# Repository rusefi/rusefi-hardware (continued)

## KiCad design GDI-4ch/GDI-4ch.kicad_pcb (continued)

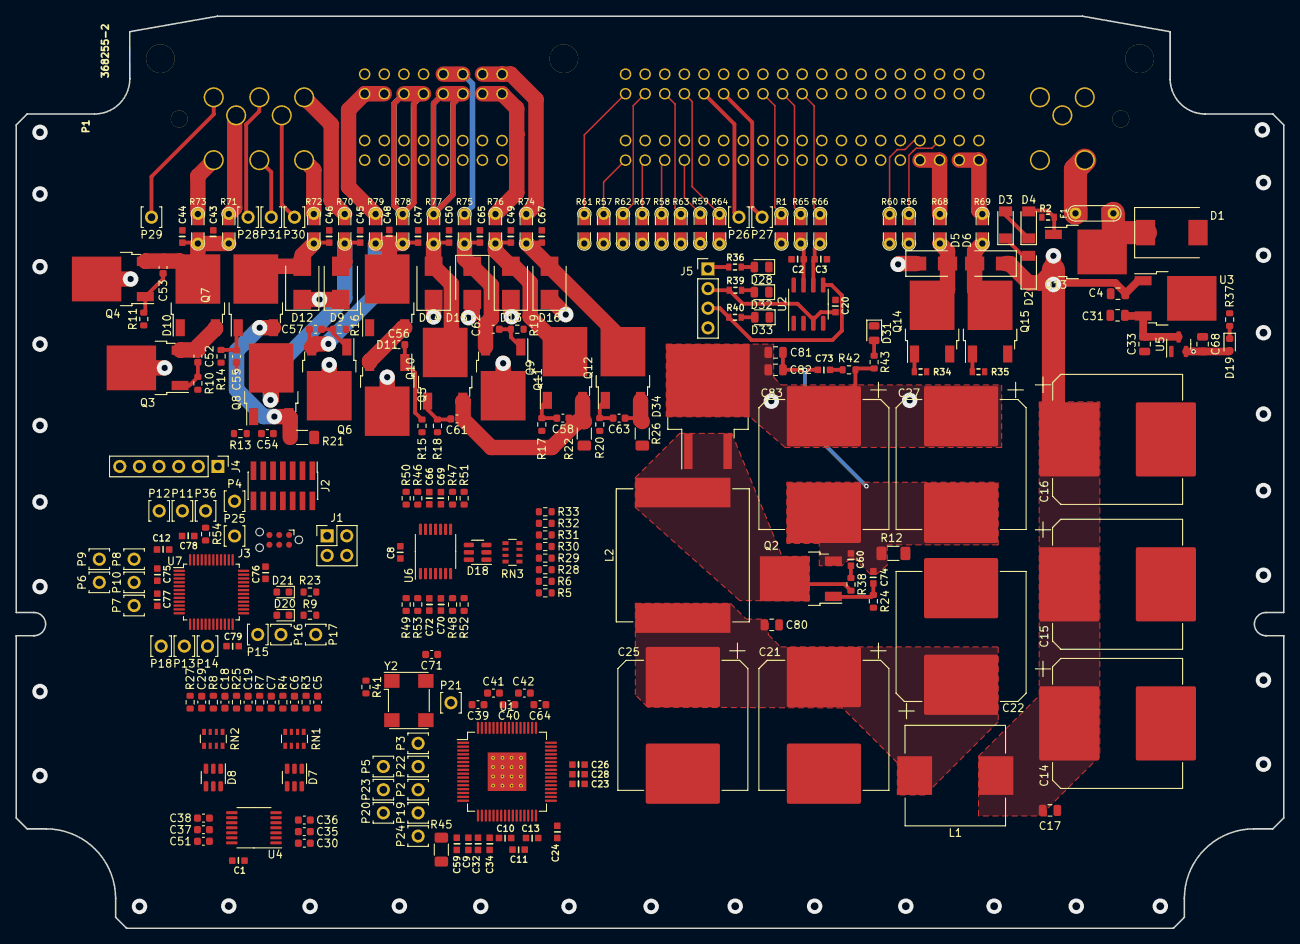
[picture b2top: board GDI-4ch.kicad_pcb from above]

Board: 4 copper layers, 164.0 x 118.0 mm, 250 parts (0 on the bottom side), 176 nets.

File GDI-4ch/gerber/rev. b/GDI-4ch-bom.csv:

Comment,Designator,Footprint,LCSC
"100n","C1,C8,C20,C23,C28,C32,C34,C59,C66,C69,C70,C72,C75,C76,C77,C78,C79","hellen-one-common:C0603","C14663"
"330p","C10,C11,C13,C24,C60,C73","hellen-one-common:C0603","C576850"
"4.7u","C12,C26","hellen-one-common:C0603","C19666"
"390uF","C14,C15,C16,C21,C22,C25,C27,C83","Capacitor_SMD:CP_Elec_16x17.5","C487421"
"0.22uF","C17,C80,C81,C82","Capacitor_SMD:C_0805_2012Metric","C342873"
"47p","C2,C3","hellen-one-common:C0603","C1671"
"0.33uF","C39,C40,C41,C42,C64","Capacitor_SMD:C_0603_1608Metric","C1615"
"10u","C4,C31,C33,C68","Capacitor_SMD:C_0805_2012Metric","C15850"
"4700p","C43,C44,C45,C46,C47,C48,C49,C50,C65,C67","hellen-one-common:C0603","C342899"
"1000pF","C5,C6,C7,C18,C19,C29,C30,C35,C36,C37,C38,C51,C52,C53,C54,C55,C56,C57,C58,C61,C62,C63,C71","Capacitor_SMD:C_0603_1608Metric","C106247"
"470p","C74","hellen-one-common:C0603","C326973"
"1u","C9","hellen-one-common:C0603","C15849"
"SMCJ22CA","D1","Diode_SMD:D_SMC","C310038"
"SBR10200CTL","D10,D11","Package_TO_SOT_SMD:TO-252-2","C135494"
"WHITE","D19","LED_SMD:LED_0603_1608Metric","C2290"
"ZMM5V6","D2,D3,D4","Diode_SMD:D_MiniMELF","C8062"
"BLUE","D20","LED_SMD:LED_0603_1608Metric","C72041"
"GREEN","D21","LED_SMD:LED_0603_1608Metric","C72043"
"LED_Small","D28,D31,D32,D33","LED_SMD:LED_0805_2012Metric","C2296"
"SDURB1020CT","D34","Package_TO_SOT_SMD:TO-263-2","C260365"
"D_Schottky","D5,D6","Diode_SMD:D_SMA","C8678"
"SRV05-4","D7,D8,D18","Package_TO_SOT_SMD:SOT-23-6","C85364"
"STPS2H100UY","D9,D12,D13,D14,D15,D16","Diode_SMD:D_SMB","C163541"
"Fuse-Pad-Pad","F1","hellen-one-common:PAD-1206-PAD","C310989"
"RUSEFI_LOGO","G1","kicad6-libraries:rusefi_logo",""
"Conn_02x02_Odd_Even","J1","Connector_PinHeader_2.54mm:PinHeader_2x02_P2.54mm_Vertical",""
"FTSH-107-01-F-DV-K","J2","Connector_PinHeader_1.27mm:PinHeader_2x07_P1.27mm_Vertical_SMD",""
"Conn_01x06","J4","Connector_PinHeader_2.54mm:PinHeader_1x06_P2.54mm_Vertical",""
"Conn_01x04","J5","Connector_PinHeader_2.54mm:PinHeader_1x04_P2.54mm_Vertical",""
"6.8uH","L1","Inductor_SMD:L_Wuerth_HCI-1350","C380073"
"10uH","L2","Inductor_SMD:L_Vishay_IHLP-6767","C237980"
"368255-2","P1","kicad6-libraries:TE_368255-2",""
"Pad","P2,P3,P4,P5,P6,P7,P8,P9,P10,P11,P18,P19,P20,P25,P26,P27,P28,P29,P30,P31,P32,P36","hellen-one-common:PAD-TH",""
"AOD4185","Q13","Package_TO_SOT_SMD:TO-252-2","C400894"
"VND14NV04TR-E","Q14,Q15","Package_TO_SOT_SMD:TO-252-2","C2649436"
"BUK9230-100B","Q2,Q3,Q4,Q5,Q6,Q7,Q8,Q9,Q10,Q11,Q12","Package_TO_SOT_SMD:TO-252-2","C89735"
"DNP","R1,R44,R55,R60,R80,R81,R82,R83","hellen-one-common:PAD-0805-PAD",""
"10","R10,R11,R13,R14,R15,R16,R17,R18,R19,R20,R24","Resistor_SMD:R_0603_1608Metric","C22859"
"0.01","R12,R21,R22,R26,R45","kicad6-libraries:Shunt_1206","C309628"
"10k","R2,R34,R35","hellen-one-common:R0603","C25804"
"1K","R3,R4,R7,R8,R9,R23,R25,R27,R37","Resistor_SMD:R_0603_1608Metric","C21190"
"5.1k","R36","hellen-one-common:R0603","C23186"
"5.1","R38,R42","Resistor_SMD:R_0603_1608Metric","C25197"
"1.6k","R39","hellen-one-common:R0603","C22847"
"750","R40","hellen-one-common:R0603","C23241"
"75K","R43","Resistor_SMD:R_0603_1608Metric","C23242"
"6.8K","R46,R47,R48,R49","Resistor_SMD:R_0603_1608Metric","C23212"
"DNP","R5,R28,R30,R32","Resistor_SMD:R_0603_1608Metric",""
"10K","R50,R51,R52,R53,R54","Resistor_SMD:R_0603_1608Metric","C25804"
"Jumper-Pad-Pad","R56,R57,R58,R59,R61,R62,R63,R64,R65,R66,R67,R68,R69,R70,R71,R72,R73,R74,R75,R76,R77,R78,R79","hellen-one-common:PAD-0805-PAD","C17477"
"470K","R6,R29,R31,R33","Resistor_SMD:R_0603_1608Metric","C23178"
"10k","RN1,RN2,RN3","Resistor_SMD:R_Array_Convex_4x0603","C29718"
"MC33816","U1","Package_QFP:LQFP-64-1EP_10x10mm_P0.5mm_EP5x5mm_ThermalVias",""
"TJA1051T-3","U2","Package_SO:SOIC-8_3.9x4.9mm_P1.27mm","C38695"
"LM78M05_TO252","U3","Package_TO_SOT_SMD:TO-252-2","C58069"
"74HC14","U4","Package_SO:TSSOP-14_4.4x5mm_P0.65mm","C5606"
"XC6206P332MR","U5","Package_TO_SOT_SMD:SOT-23","C5446"
"MCP6004","U6","Package_SO:TSSOP-14_4.4x5mm_P0.65mm","C248577"
"STM32F103C8Tx","U7","Package_QFP:LQFP-48_7x7mm_P0.5mm","C8734"
"1MHz","Y2","Oscillator:Oscillator_SMD_Diodes_FN-4Pin_7.0x5.0mm","C70608"

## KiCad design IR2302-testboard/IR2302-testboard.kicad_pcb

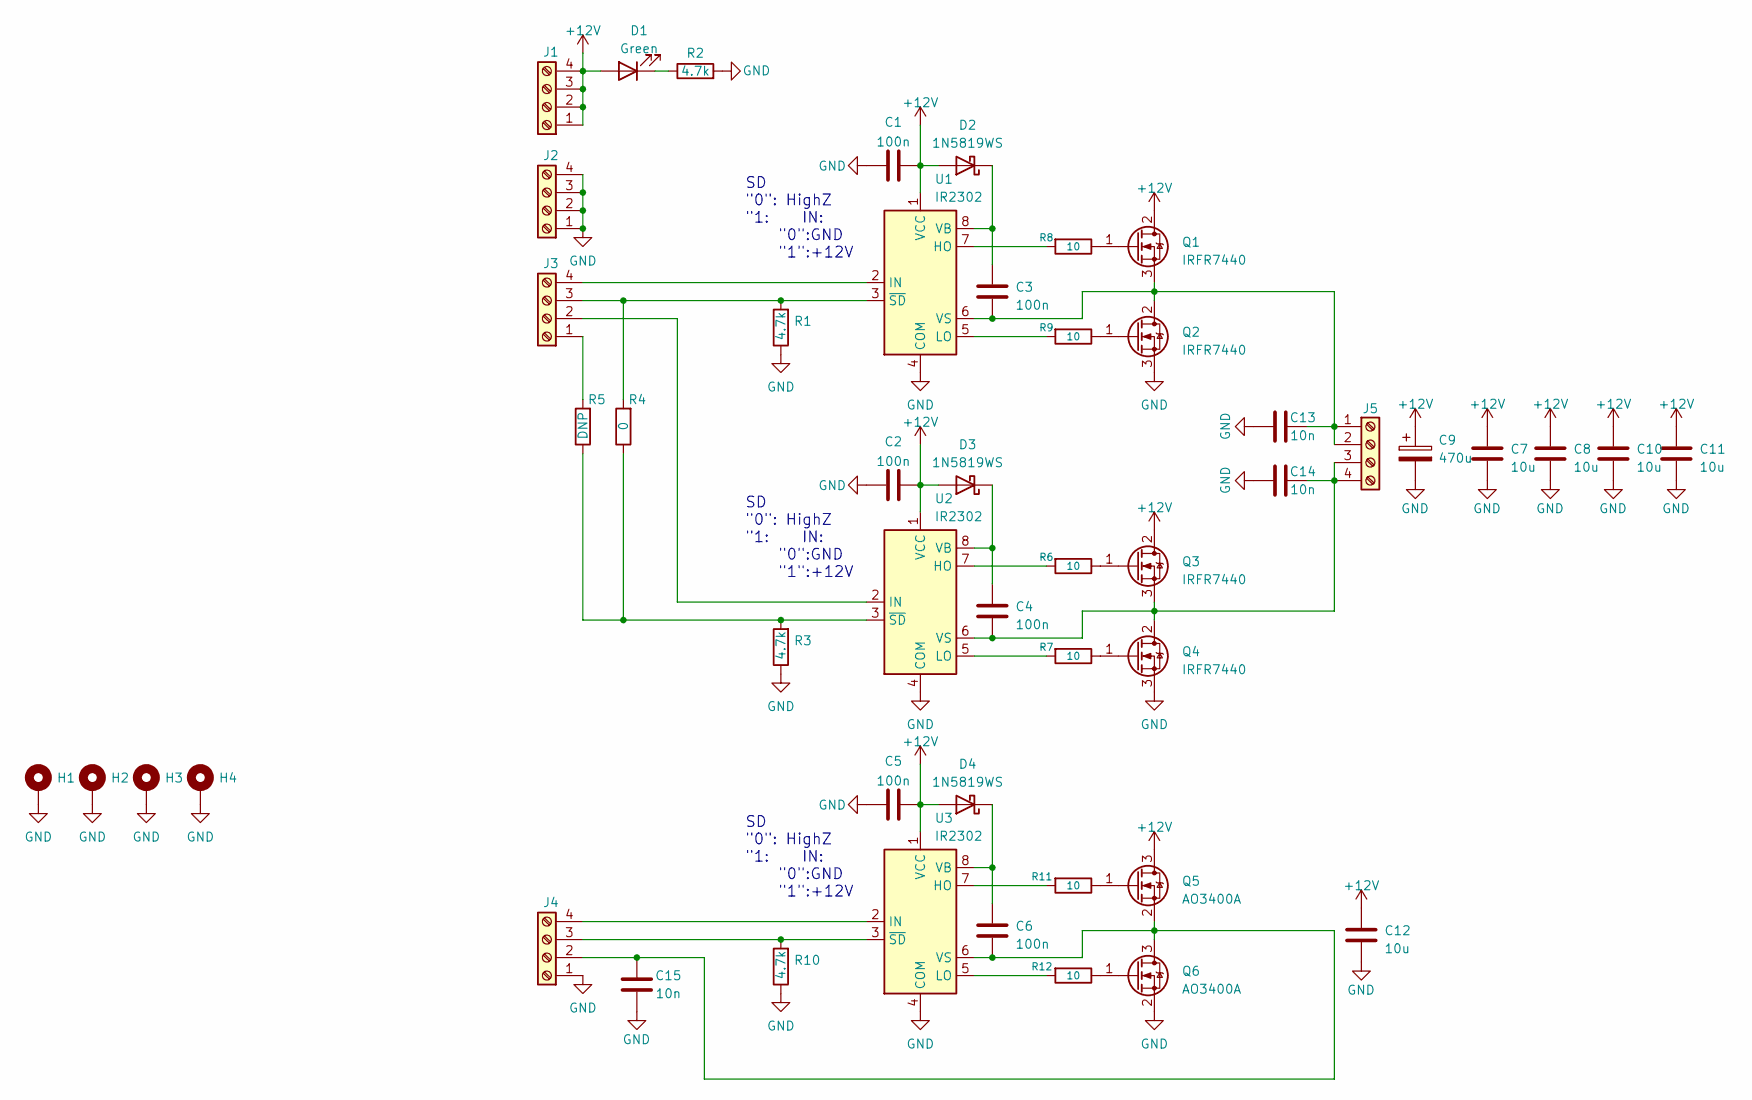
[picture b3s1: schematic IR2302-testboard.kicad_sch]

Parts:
C1, C2, C3, C4, C5, C6: 100n; C_0603_1608Metric_Pad1.08x0.95mm_HandSolder; LCSC C14663
C7, C8, C10, C11, C12: 10u; C_0805_2012Metric_Pad1.18x1.45mm_HandSolder; LCSC C15850
C9: 470u; CP_Elec_10x10.5; LCSC C72518
C13, C14, C15: 10n; C_0603_1608Metric_Pad1.08x0.95mm_HandSolder; LCSC C57112
D1: Green; LED_0805_2012Metric_Pad1.15x1.40mm_HandSolder; LCSC C2297
D2, D3, D4: 1N5819WS; D_SOD-323; LCSC C191023
H1, H2, H3, H4: MountingHole_Pad; MountingHole_3.2mm_M3_Pad_Via
J1, J2, J3, J4, J5: Screw_Terminal_01x04; TerminalBlock_MetzConnect_Type055_RT01504HDWU_1x04_P5.00mm_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; LCSC C173286
Q1, Q2, Q3, Q4: IRFR7440; TO-252-2; LCSC C97244
Q5, Q6: AO3400A; SOT-23; LCSC C20917
R1, R2, R3, R10: 4.7k; R_0603_1608Metric_Pad0.98x0.95mm_HandSolder; LCSC C23162
R4: 0; R_0603_1608Metric_Pad0.98x0.95mm_HandSolder; LCSC C21189
R5: DNP; R_0603_1608Metric_Pad0.98x0.95mm_HandSolder
R6, R7, R8, R9, R11, R12: 10; R_0603_1608Metric; LCSC C22859
U1, U2, U3: IR2302; SO-8_3.9x4.9mm_P1.27mm; LCSC C148147

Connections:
+12V: C1.2, C2.2, C5.2, C7.2, C8.2, C9.1, C10.2, C11.2, C12.2, D1.2 (A), D2.2 (A), D3.2 (A), D4.2 (A), J1.1, J1.2, J1.3, J1.4, Q1.2 (D), Q3.2 (D), Q5.3 (D), U1.1 (VCC), U2.1 (VCC), U3.1 (VCC)
GND: C1.1, C2.1, C5.1, C7.1, C8.1, C9.2, C10.1, C11.1, C12.1, C13.1, C14.1, C15.1, H1.1, H2.1, H3.1, H4.1, J2.1, J2.2, J2.3, J2.4, J4.1, Q2.3 (S), Q4.3 (S), Q6.2 (S), R1.1, R2.2, R3.1, R10.1, U1.4 (COM), U2.4 (COM), U3.4 (COM)
unnamed: D1.1 (K), R2.1
unnamed: C3.1, D2.1 (K), U1.8 (VB)
unnamed: C4.1, D3.1 (K), U2.8 (VB)
unnamed: C6.1, D4.1 (K), U3.8 (VB)
unnamed: J3.1, R5.2
unnamed: J3.2, U2.2 (IN)
unnamed: J3.3, R1.2, R4.2, U1.3 (~SD)
unnamed: J3.4, U1.2 (IN)
unnamed: C6.2, C15.2, J4.2, Q5.2 (S), Q6.3 (D), U3.6 (VS)
unnamed: J4.3, R10.2, U3.3 (~SD)
unnamed: J4.4, U3.2 (IN)
unnamed: C3.2, C13.2, J5.1, J5.2, Q1.3 (S), Q2.2 (D), U1.6 (VS)
unnamed: C4.2, C14.2, J5.3, J5.4, Q3.3 (S), Q4.2 (D), U2.6 (VS)
unnamed: Q1.1 (G), R8.1
unnamed: Q2.1 (G), R9.1
unnamed: Q3.1 (G), R6.1
unnamed: Q4.1 (G), R7.1
unnamed: Q5.1 (G), R11.1
unnamed: Q6.1 (G), R12.1
unnamed: R8.2, U1.7 (HO)
unnamed: R9.2, U1.5 (LO)
unnamed: R6.2, U2.7 (HO)
unnamed: R7.2, U2.5 (LO)
unnamed: R3.2, R4.1, R5.1, U2.3 (~SD)
unnamed: R11.2, U3.7 (HO)
unnamed: R12.2, U3.5 (LO)

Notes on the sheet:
SD "0": HighZ "1: IN: "0":GND "1":+12V

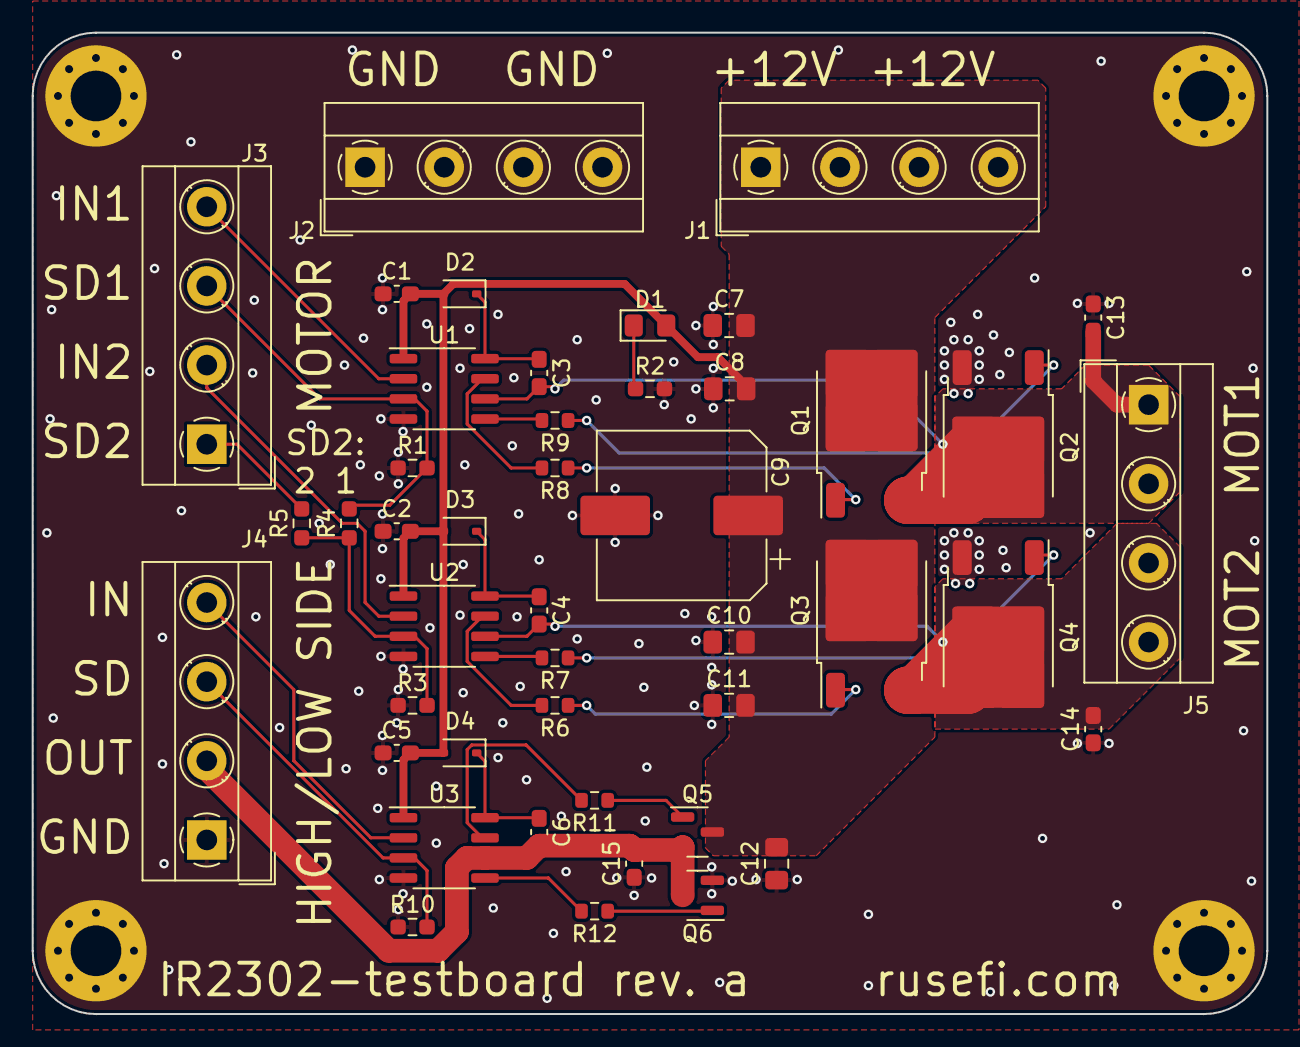
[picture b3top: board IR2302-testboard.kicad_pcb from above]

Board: 2 copper layers, 78.0 x 62.0 mm, 49 parts (0 on the bottom side), 28 nets.

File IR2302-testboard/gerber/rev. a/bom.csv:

Designator,Footprint,Quantity,Value,LCSC Part #
"C1, C2, C3, C4, C5, C6",0603,6,100n,C14663
"C10, C11, C12, C7, C8",0805,5,10u,C15850
"C13, C14, C15",0603,3,10n,C57112
C9,CP_Elec_10x10.5,1,470u,C72518
D1,0805,1,Green,C2297
"D2, D3, D4",D_SOD-323,3,1N5819WS,C191023
"H1, H2, H3, H4",MountingHole_3.2mm_M3_Pad_Via,4,MountingHole_Pad,
"J1, J2, J3, J4, J5",TerminalBlock_MetzConnect_Type055_RT01504HDWU_1x04_P5.00mm_Horizontal,5,Screw_Terminal_01x04,C173286
"Q1, Q2, Q3, Q4",TO-252-2,4,IRFR7440,C97244
"Q5, Q6",SOT-23,2,AO3400A,C20917
"R1, R10, R2, R3",0603,4,4.7k,C23162
"R11, R12, R6, R7, R8, R9",0603,6,10,C22859
R4,0603,1,0,C21189
R5,0603,1,DNP,
"U1, U2, U3",SO-8_3.9x4.9mm_P1.27mm,3,IR2302,C148147

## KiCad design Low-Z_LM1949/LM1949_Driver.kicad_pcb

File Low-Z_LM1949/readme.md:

https://www.ti.com/product/LM1949

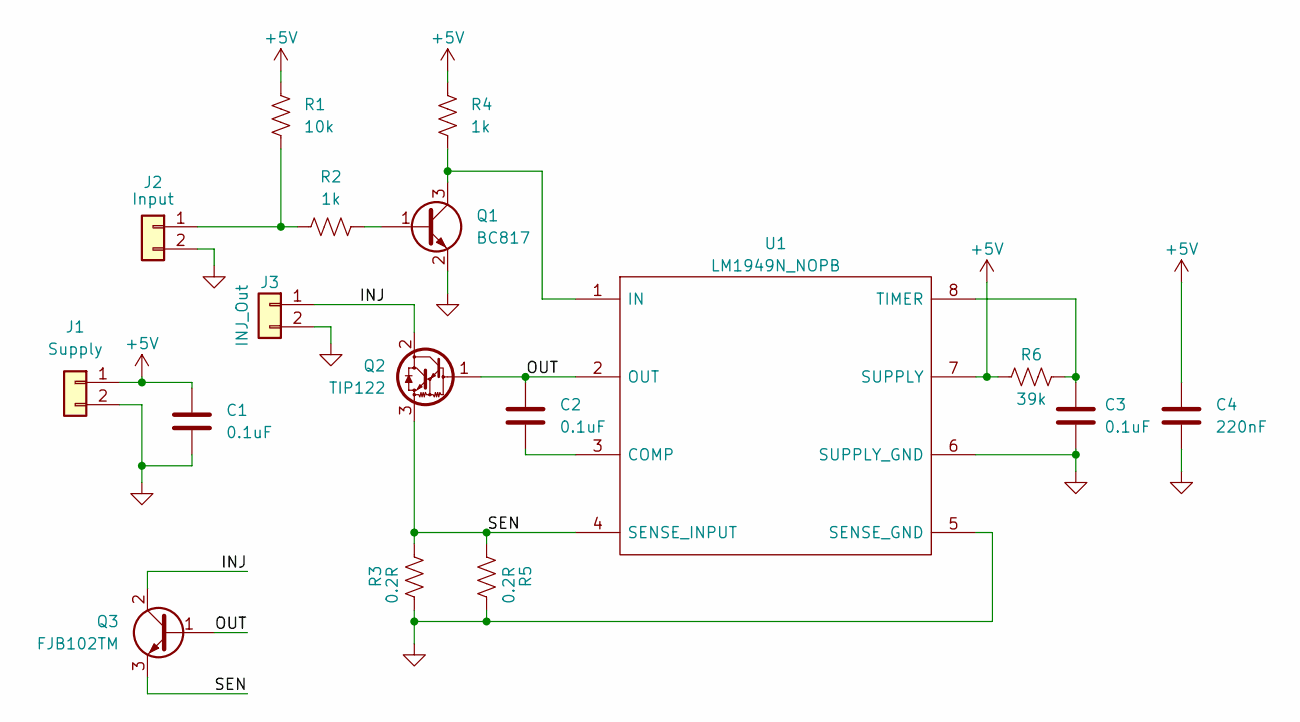
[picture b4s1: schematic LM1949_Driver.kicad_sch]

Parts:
C1, C2, C3: 0.1uF; C_0805_2012Metric_Pad1.18x1.45mm_HandSolder; JLC Pt. Num C126469
C4: 220nF; CP_EIA-3216-18_Kemet-A_Pad1.58x1.35mm_HandSolder; JLC Pt. Num C11364
J1: Supply; TerminalBlock_Phoenix_PT-1,5-2-5.0-H_1x02_P5.00mm_Horizontal; JLC Pt. Num NC
J2: Input; TerminalBlock_Phoenix_PT-1,5-2-5.0-H_1x02_P5.00mm_Horizontal; JLC Pt. Num NC
J3: INJ_Out; TerminalBlock_Phoenix_PT-1,5-2-5.0-H_1x02_P5.00mm_Horizontal; JLC Pt. Num NC
Q1: BC817; SOT-23; JLC Pt. Num C475629
Q2: TIP122; TO-220-3_Vertical; JLC Pt. Num C16283
Q3: FJB102TM; TO-263-2; JLC Pt. Num NC
R1: 10k; R_0805_2012Metric_Pad1.20x1.40mm_HandSolder; JLC Pt. Num C416062
R2, R4: 1k; R_0805_2012Metric_Pad1.20x1.40mm_HandSolder; JLC Pt. Num C100046
R3, R5: 0.2R; R_2512_6332Metric_Pad1.40x3.35mm_HandSolder; JLC Pt. Num C176047
R6: 39k; R_0805_2012Metric_Pad1.20x1.40mm_HandSolder; JLC Pt. Num C416101
U1: LM1949N_NOPB; DIP-8_W7.62mm_LongPads; JLC Pt. Num NC

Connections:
+5V: C1.1, C4.1, J1.1, R1.1, R4.1, R6.1, U1.7 (SUPPLY)
/INJ: J3.1, Q2.2 (C), Q3.2 (C)
/OUT: C2.1, Q2.1 (B), Q3.1 (B), U1.2 (OUT)
/SEN: Q2.3 (E), Q3.3 (E), R3.1, R5.1, U1.4 (SENSE_INPUT)
GND: C1.2, C3.2, C4.2, J1.2, J2.2, J3.2, Q1.2 (E), R3.2, R5.2, U1.5 (SENSE_GND), U1.6 (SUPPLY_GND)
unnamed: C2.2, U1.3 (COMP)
unnamed: C3.1, R6.2, U1.8 (TIMER)
unnamed: J2.1, R1.2, R2.1
unnamed: Q1.1 (B), R2.2
unnamed: Q1.3 (C), R4.2, U1.1 (IN)

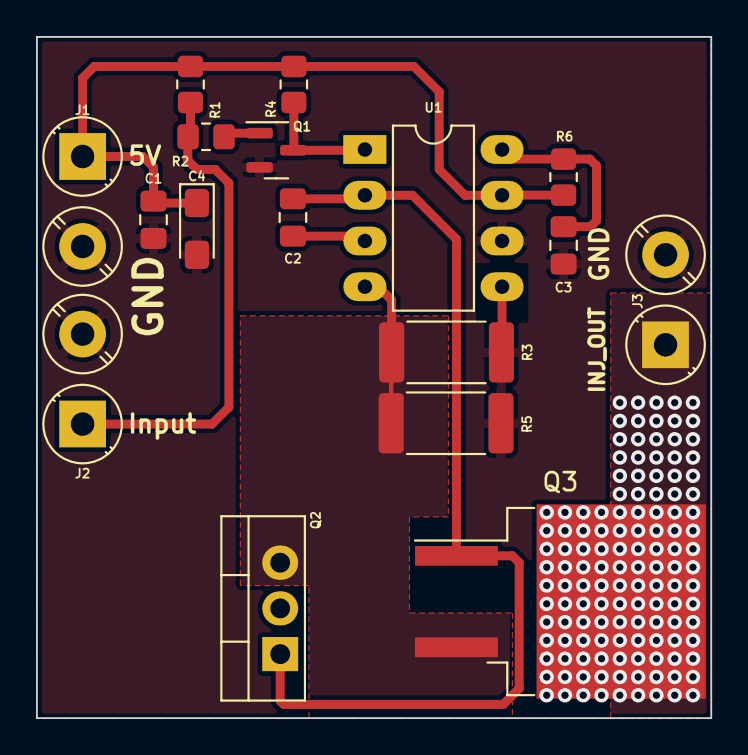
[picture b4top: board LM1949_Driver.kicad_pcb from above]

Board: 2 copper layers, 37.5 x 37.8 mm, 17 parts (0 on the bottom side), 10 nets.

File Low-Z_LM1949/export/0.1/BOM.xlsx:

Comment | Designator | Footprint | LCSC Part Number
0.1uF | C1,C2,C3 | Capacitor_SMD:C_0805_2012Metric_Pad1.18x1.45mm_HandSolder | C126469
220nF | C4 | Capacitor_Tantalum_SMD:CP_EIA-3216-18_Kemet-A_Pad1.58x1.35mm_HandSolder | C11364
BC817 | Q1 | Package_TO_SOT_SMD:SOT-23 | C475629
TIP122 | Q2 | Package_TO_SOT_THT:TO-220-3_Vertical | C16283
10k | R1 | Resistor_SMD:R_0805_2012Metric_Pad1.20x1.40mm_HandSolder | C416062
1k | R2,R4 | Resistor_SMD:R_0805_2012Metric_Pad1.20x1.40mm_HandSolder | C100046
0.2R | R3,R5 | Resistor_SMD:R_0805_2012Metric_Pad1.20x1.40mm_HandSolder | C176047
39k | R6 | Resistor_SMD:R_0805_2012Metric_Pad1.20x1.40mm_HandSolder | C416101

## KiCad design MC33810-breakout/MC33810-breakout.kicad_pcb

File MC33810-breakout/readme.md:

https://www.nxp.com/products/power-management/smart-switches-and-drivers/low-side-switches/automotive-engine-control-ic:MC33810

https://github.com/andreika-git/hellen-one/issues/173

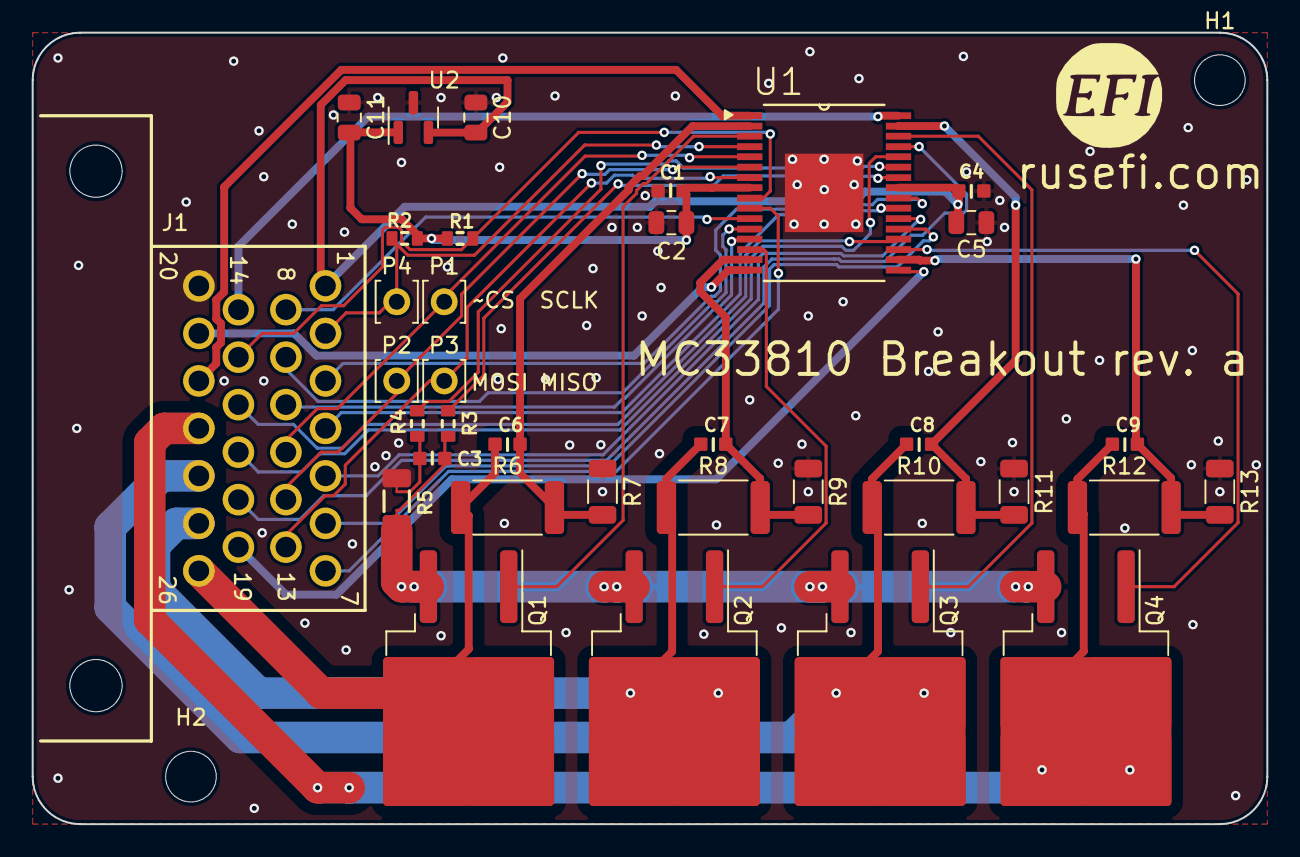
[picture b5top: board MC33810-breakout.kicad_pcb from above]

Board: 2 copper layers, 78.0 x 50.0 mm, 38 parts (0 on the bottom side), 40 nets.

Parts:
C1, C4, C6, C7, C8, C9: 100n; C0603
C2, C5, C10, C11: 10u; C_0805_2012Metric
C3: 100p; C0603
G1: RUSEFI_LOGO; rusefi_logo
H1, H2: M3; MountingHole_3.2mm_M3_ISO14580
J1: 6473423-1
P1, P2, P3, P4: Pad; PAD-TH
Q1, Q2, Q3, Q4: ISL9V3040S3S; TO-263-2
R1, R2: 10k; R0603
R3, R4: 100; R0603
R5: 0.02; Shunt_1206
R6, R8, R10, R12: 36k; R_2512_6332Metric
R7, R9, R11, R13: 4.02k; R_1206_3216Metric
U1: MCZ33810EK; Mcz33810
U2: XC6202P332MR-G; SOT-23

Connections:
+3.3V: C1.1, C2.2, C11.2, R1.2, R2.2, U1.8 (VDD), U2.1 (VO)
+BATT: C4.1, C5.2, C10.2, J1.1 (1B), U1.25 (VPWR), U2.2 (VI)
/IGN1: J1.3 (3B), U1.24 (GIN0)
/IGN2: J1.4 (4B), U1.23 (GIN1)
/IGN3: J1.5 (5B), U1.22 (GIN2)
/IGN4: J1.6 (6B), U1.21 (GIN3)
/INJ1: J1.7 (7B), U1.10 (DIN0)
/INJ2: J1.8 (8B), U1.11 (DIN1)
/INJ3: J1.9 (9B), U1.12 (DIN2)
/INJ4: J1.10 (10B), U1.13 (DIN3)
/MAXI: J1.18 (18B), U1.29 (MAXI)
/MISO: J1.13 (13B), P3.1, U1.7 (SO)
/MOSI: J1.12 (12B), P2.1, U1.6 (SI)
/NOMI: J1.17 (17B), U1.28 (NOMI)
/OUT_IGN1: C6.1, J1.26 (26B), Q1.2 (C), R6.1
/OUT_IGN2: C7.1, J1.25 (25B), Q2.2 (C), R8.1
/OUT_IGN3: C8.1, J1.24 (24B), Q3.2 (C), R10.1
/OUT_IGN4: C9.1, J1.23 (23B), Q4.2 (C), R12.1
/OUT_INJ1: J1.22 (22B), U1.1 (OUT0)
/OUT_INJ2: J1.21 (21B), U1.16 (OUT1)
/OUT_INJ3: J1.14 (14B), U1.32 (OUT2)
/OUT_INJ4: J1.19 (19B), U1.17 (OUT3)
/SCLK: J1.11 (11B), P1.1, U1.5 (SCLK)
/~CS: J1.2 (2B), P4.1, R2.1, U1.4 (~CS)
/~OUTEN: J1.15 (15B), R1.1, U1.9 (~OUTEN)
/~SPKDUR: J1.16 (16B), U1.20 (~SPKDUR)
GND: C1.2, C2.1, C4.2, C5.1, C10.1, C11.1, J1.20 (20B), R5.4, R7.2, R9.2, R11.2, R13.2, U1.33 (GND), U2.3 (GND)
unnamed: C3.1, R3.2, R5.2
unnamed: C3.2, R4.2, R5.3
unnamed: Q1.3 (E), Q2.3 (E), Q3.3 (E), Q4.3 (E), R5.1
unnamed: Q1.1 (G), U1.3 (GD0)
unnamed: Q2.1 (G), U1.14 (GD1)
unnamed: Q3.1 (G), U1.30 (GD2)
unnamed: Q4.1 (G), U1.19 (GD3)
unnamed: C6.2, R6.2, R7.1, U1.2 (FB0)
unnamed: C7.2, R8.2, R9.1, U1.15 (FB1)
unnamed: C8.2, R10.2, R11.1, U1.31 (FB2)
unnamed: C9.2, R12.2, R13.1, U1.18 (FB3)
unnamed: R4.1, U1.27 (RSN)
unnamed: R3.1, U1.26 (RSP)

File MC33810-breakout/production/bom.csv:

Designator,Footprint,Quantity,Value,LCSC Part #
"C1, C4, C6, C7, C8, C9",C0603,6,100n,C14663
"C10, C11, C2, C5",0805,4,10u,C15850
C3,C0603,1,100p,C14858
G1,rusefi_logo,1,RUSEFI_LOGO,
"H1, H2",MountingHole_3.2mm_M3_ISO14580,2,M3,
J1,6473423-1,1,6473423-1,
"P1, P2, P3, P4",PAD-TH,4,Pad,
"Q1, Q2, Q3, Q4",TO-263-2,4,ISL9V3040S3S,C898702
"R1, R2",R0603,2,10k,C25804
"R10, R12, R6, R8",2512,4,36k,C474088
"R11, R13, R7, R9",1206,4,4.02k,C274026
"R3, R4",R0603,2,100,C22775
R5,Shunt_1206,1,0.02,C728292
U1,Mcz33810,1,MCZ33810EK,C3192631
U2,SOT-23,1,XC6202P332MR-G,C47374

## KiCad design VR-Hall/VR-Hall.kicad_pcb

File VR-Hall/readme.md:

VR/Hall mixing test board

Problem statement: do do not have x8 or x10 position sensor inputs on stm32, in order to handle any combination of x5 hall and x3/x5 VRs we would need to mix each VR with Hall

We are looking to confirm that VR signal (in this case from MAX9924) could be mixed with Hall signal into same/shared digital signal

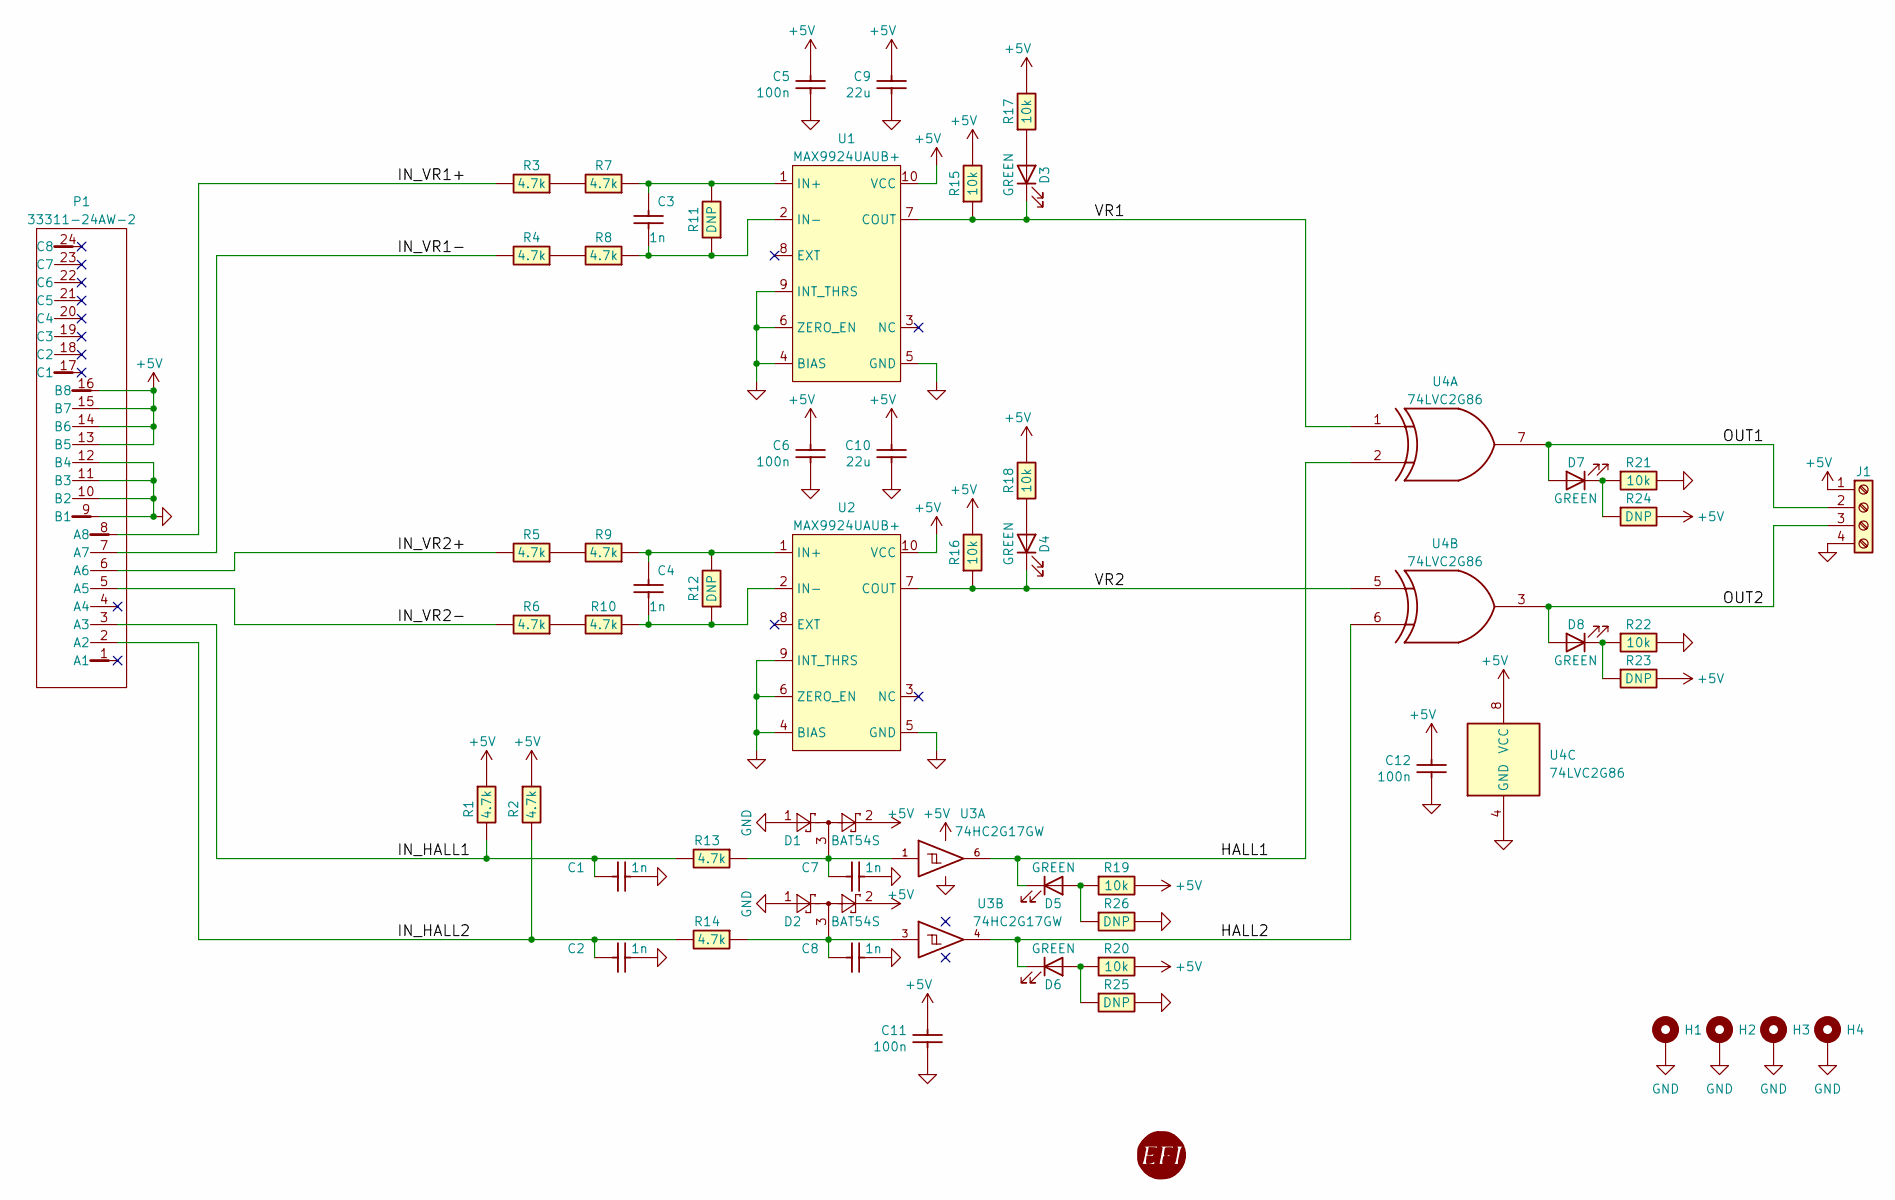
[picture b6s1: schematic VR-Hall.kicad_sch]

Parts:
C1, C2, C3, C4, C7, C8: 1n; C0603; LCSC C1588
C5, C6, C11, C12: 100n; C0603; LCSC C14663
C9, C10: 22u; C0603; LCSC C59461
D1, D2: BAT54S; SOT-23; LCSC C408389
D3, D4, D5, D6, D7, D8: GREEN; LED_0603_1608Metric; LCSC C72043
G1: RUSEFI_LOGO; rusefi_logo
H1, H2, H3, H4: MountingHole_Pad; MountingHole_3.2mm_M3_Pad_Via
J1: DNP; TerminalBlock_MetzConnect_Type055_RT01504HDWU_1x04_P5.00mm_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
P1: 33311-24AW-2
R1, R2, R13, R14: 4.7k; R0603; LCSC C23162
R3, R4, R5, R6, R7, R8, R9, R10: 4.7k; R1206; LCSC C17936
R11, R12, R23, R24, R25, R26: DNP; R0603
R15, R16, R17, R18, R19, R20, R21, R22: 10k; R0603; LCSC C25804
U1, U2: MAX9924UAUB+; MSOP-10_3x3mm_P0.5mm; LCSC C143633
U3: 74HC2G17GW; SOT-363; LCSC C94189
U4: 74LVC2G86; MSOP-8_3x3mm_P0.65mm; LCSC C130023

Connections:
+5V: C5.2, C6.2, C9.2, C10.2, C11.2, C12.2, D1.2, D2.2, J1.1, P1.13 (B5), P1.14 (B6), P1.15 (B7), P1.16 (B8), R1.1, R2.1, R15.2, R16.2, R17.2, R18.2, R19.2, R20.2, R23.2, R24.2, U1.10 (VCC), U2.10 (VCC), U3.5 (VCC), U4.8 (VCC)
/HALL1: D5.1 (K), U3.6, U4.2
/HALL2: D6.1 (K), U3.4, U4.6
/IN_HALL1: C1.1, P1.3 (A3), R1.2, R13.2
/IN_HALL2: C2.1, P1.2 (A2), R2.2, R14.2
/IN_VR1+: P1.8 (A8), R3.2
/IN_VR1-: P1.7 (A7), R4.2
/IN_VR2+: P1.6 (A6), R5.2
/IN_VR2-: P1.5 (A5), R6.2
/OUT1: D7.2 (A), J1.2, U4.7
/OUT2: D8.2 (A), J1.3, U4.3
/VR1: D3.1 (K), R15.1, U1.7 (COUT), U4.1
/VR2: D4.1 (K), R16.1, U2.7 (COUT), U4.5
GND: C1.2, C2.2, C5.1, C6.1, C7.2, C8.2, C9.1, C10.1, C11.1, C12.1, D1.1, D2.1, H1.1, H2.1, H3.1, H4.1, J1.4, P1.9 (B1), P1.10 (B2), P1.11 (B3), P1.12 (B4), R21.2, R22.2, R25.2, R26.2, U1.4 (BIAS), U1.5 (GND), U1.6 (ZERO_EN), U1.9 (INT_THRS), U2.4 (BIAS), U2.5 (GND), U2.6 (ZERO_EN), U2.9 (INT_THRS), U3.2 (GND), U4.4 (GND)
unnamed: C7.1, D1.3, R13.1, U3.1
unnamed: C8.1, D2.3, R14.1, U3.3
unnamed: D3.2 (A), R17.1
unnamed: D4.2 (A), R18.1
unnamed: D5.2 (A), R19.1, R26.1
unnamed: D6.2 (A), R20.1, R25.1
unnamed: D7.1 (K), R21.1, R24.1
unnamed: D8.1 (K), R22.1, R23.1
unnamed: R3.1, R7.2
unnamed: R4.1, R8.2
unnamed: R5.1, R9.2
unnamed: R6.1, R10.2
unnamed: C3.2, R7.1, R11.2, U1.1 (IN+)
unnamed: C3.1, R8.1, R11.1, U1.2 (IN-)
unnamed: C4.2, R9.1, R12.2, U2.1 (IN+)
unnamed: C4.1, R10.1, R12.1, U2.2 (IN-)

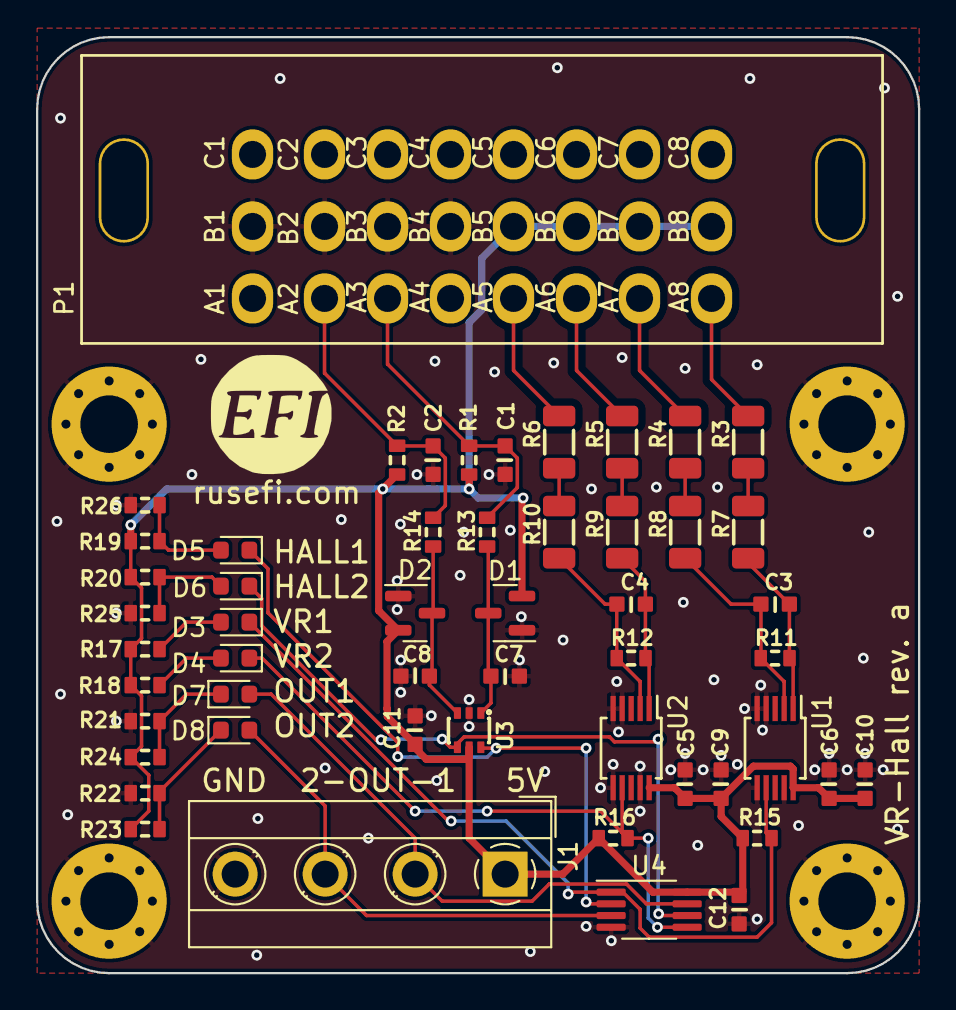
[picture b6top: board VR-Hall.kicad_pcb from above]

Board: 2 copper layers, 49.0 x 52.0 mm, 57 parts (0 on the bottom side), 30 nets.

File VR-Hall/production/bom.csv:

Designator,Footprint,Quantity,Value,LCSC Part #
"C1, C2, C3, C4, C7, C8",C0603,6,1n,C1588
"C10, C9",C0603,2,22u,C59461
"C11, C12, C5, C6",C0603,4,100n,C14663
"D1, D2",SOT-23,2,BAT54S,C408389
"D3, D4, D5, D6, D7, D8",0603,6,GREEN,C72043
G1,rusefi_logo,1,RUSEFI_LOGO,
"H1, H2, H3, H4",MountingHole_3.2mm_M3_Pad_Via,4,MountingHole_Pad,
J1,TerminalBlock_MetzConnect_Type055_RT01504HDWU_1x04_P5.00mm_Horizontal,1,DNP,
P1,33311-24AW-2,1,33311-24AW-2,
"R1, R13, R14, R2",R0603,4,4.7k,C23162
"R10, R3, R4, R5, R6, R7, R8, R9",R1206,8,4.7k,C17936
"R11, R12, R23, R24, R25, R26",R0603,6,DNP,
"R15, R16, R17, R18, R19, R20, R21, R22",R0603,8,10k,C25804
"U1, U2",MSOP-10_3x3mm_P0.5mm,2,MAX9924UAUB+,C143633
U3,SOT-363,1,74HC2G17GW,C94189
U4,MSOP-8_3x3mm_P0.65mm,1,74LVC2G86,C130023

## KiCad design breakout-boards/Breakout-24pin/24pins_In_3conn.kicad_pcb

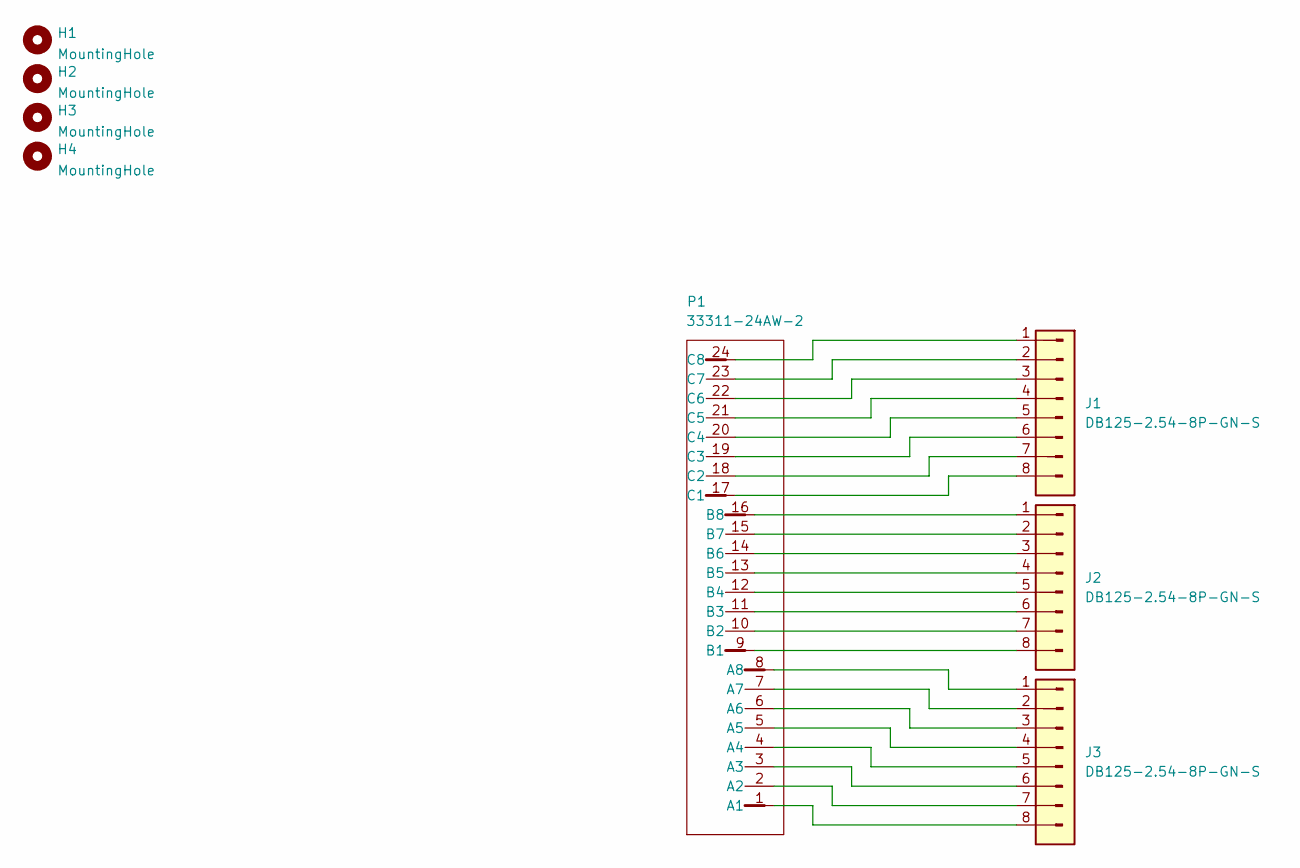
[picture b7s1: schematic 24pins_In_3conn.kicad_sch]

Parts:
H1, H2, H3, H4: MountingHole; MountingHole_3.2mm_M3_DIN965_Pad
J1, J2, J3: DB125-2.54-8P-GN-S
P1: 33311-24AW-2

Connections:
unnamed: J1.1, P1.24 (C8)
unnamed: J1.2, P1.23 (C7)
unnamed: J1.3, P1.22 (C6)
unnamed: J1.4, P1.21 (C5)
unnamed: J1.5, P1.20 (C4)
unnamed: J1.6, P1.19 (C3)
unnamed: J1.7, P1.18 (C2)
unnamed: J1.8, P1.17 (C1)
unnamed: J2.1, P1.16 (B8)
unnamed: J2.2, P1.15 (B7)
unnamed: J2.3, P1.14 (B6)
unnamed: J2.4, P1.13 (B5)
unnamed: J2.5, P1.12 (B4)
unnamed: J2.6, P1.11 (B3)
unnamed: J2.7, P1.10 (B2)
unnamed: J2.8, P1.9 (B1)
unnamed: J3.1, P1.8 (A8)
unnamed: J3.2, P1.7 (A7)
unnamed: J3.3, P1.6 (A6)
unnamed: J3.4, P1.5 (A5)
unnamed: J3.5, P1.4 (A4)
unnamed: J3.6, P1.3 (A3)
unnamed: J3.7, P1.2 (A2)
unnamed: J3.8, P1.1 (A1)

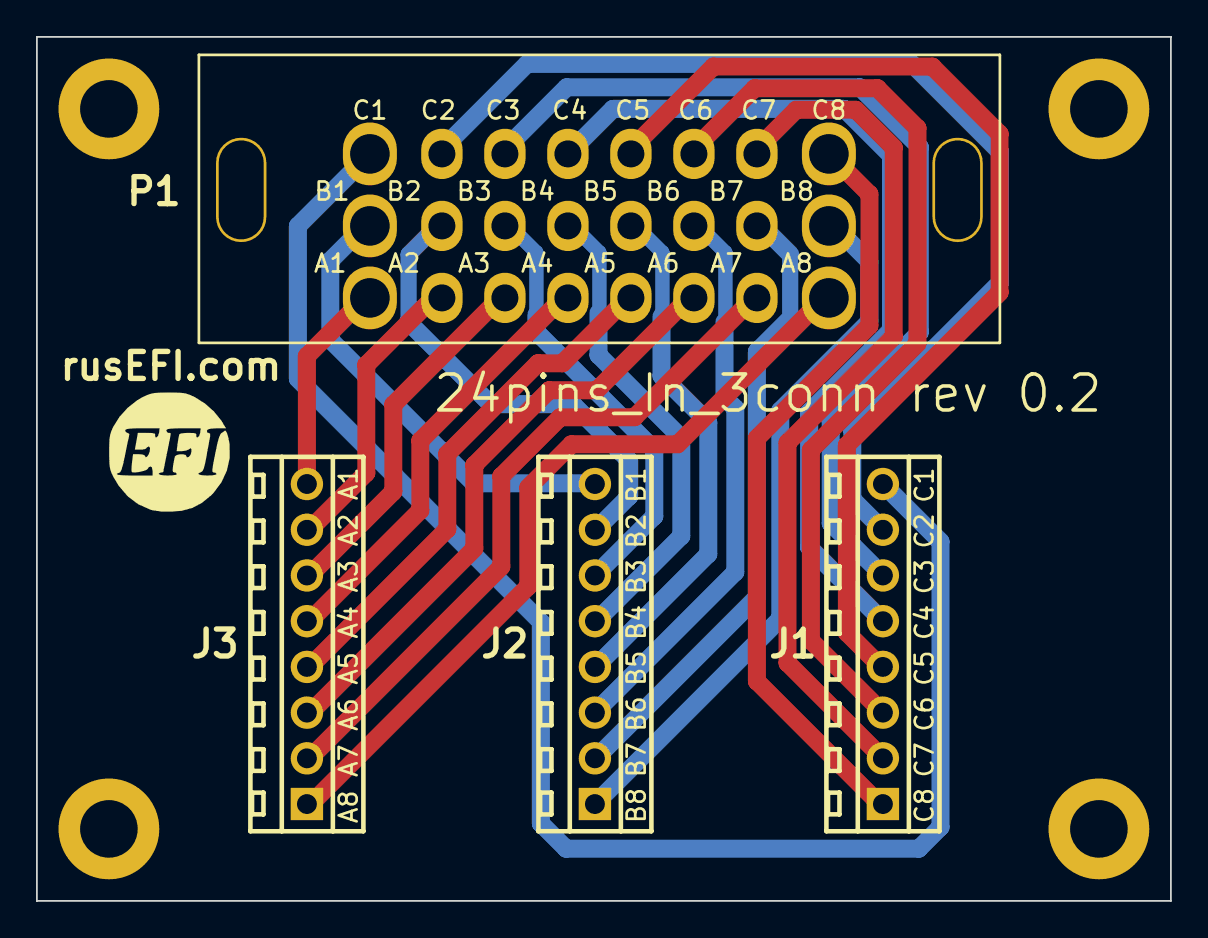
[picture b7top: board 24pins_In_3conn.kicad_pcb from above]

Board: 2 copper layers, 63.0 x 48.0 mm, 10 parts (1 on the bottom side), 24 nets.

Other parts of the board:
G?: LOGO
G?#2: LOGO
